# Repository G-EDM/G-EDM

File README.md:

</br>
</br>
</br>

```diff
 ______     _______ ______  _______
|  ____ ___ |______ |     \ |  |  |
|_____|     |______ |_____/ |  |  |      

Overview / Gateway
```                                                               

</br>
</br>

</br>
</br>

# About the project

G-EDM provides Hard- and Software solution for DIY sinker and wire EDM machining targeting the hobby market while trying to keep the project affordable and low budget compatible. While this is one of the main goals there are no compromises made in regards of precision and machine rigidity.

The project evolved over time and so did the mechanical design, the electronics and the firmware.

This repo acts as a gateway to all the other repos and is a way to start the journey into the world of DIY electrical discharge machining.

There are currently two different core version of the electronics and firmware in circulation. The EVOII/III are the initial releases. The new Gapstorm components are the current and upcoming versions. 

Since the sensing circuitry has slightly changed the Gapstorm firmware is not compatible with the EVO pulseboard.

It is possible to upgrade the EVOII and III Pulseboard to match the Gapstorms. A tutorial on how to do that will follow soon. After that upgrade those baords can be used with the new firmware.

</br></br>

# Mechanics

The repo for the new gapstorm router is available here:

[Gapstorm router](https://github.com/G-EDM/gedm-gapstorm/tree/main)

</br></br>

# Electronics

The BOM for the control unit is included on this repo:

[BOM for the control unit](./control-unit-BOM.md)

Files for the PCBs are available on PCBway. To build the electronics it requires two custom PCBs. The switching PCB and the Controlboard aka Motionboard. 

The current PCBs are the Gapstorm Pro Pulseboard and the EVOIII Motionboard.

[Gapstorm Pro Pulseboard on PCBway](https://www.pcbway.com/project/shareproject/G_EDM_Gapstorm_Pro_Pulseboard_a0db8e30.html)

[EVOIII Motionboard on PCBway](https://www.pcbway.com/project/shareproject/W532897ASC41_motionboard_evoIII_rev3_bb113e0f.html)

</br>
All files for the Gapstorm Pro Board are available here:

[Gapstorm Pro Kicad files, Gerbers etc.](https://github.com/G-EDM/Gapstorm-Pro)

</br>
Tip: The Motionboard should be mounted outside of the control box that includes the Pulseboard. One way is shown on the image below using the 3D printed EVOIII Panel.
</br></br>

More images are available here:

[Gapstorm Image gallery](https://gedm.org/photos/1/album/a655d21b876f5ba21783beb6c846ac8f)

</br></br>

# 3D printed control panel

Designed to fit a 2.8" display (see the BOM)

[EVOIII Control panel](https://github.com/G-EDM/G-EDM-EVOIII-Controlpanel)

</br></br>

# Firmware

The Repo for the Gapstorm firmware:

[Gapstorm G-RBL](https://github.com/G-EDM/G-RBLv3)

The Repo for the EVOII and EVOIII Pulseboard firmware (deprecated and not compatible with the gapstorm Pulseboard)

[EVOII/III G-RBL](https://github.com/G-EDM/G-RBL-experimental)

</br></br>

# Spool holder for P5 spools

[P5 Spool holder](https://github.com/G-EDM/spool-controller)

</br></br>

# Wiki

There is no real wiki but I posted some of the most important things on the homepage that will act like some kind of a wiki:

[G-EDM FAQ and Wiki](https://gedm.org/user/1)

</br></br>

# Contact

gedm-support@proton.me

[Join the project on Discord](https://discord.gg/vWSmpkzVrj)

[G-EDM Website](https://gedm.org)

</br>
</br>

# Donations

Bitcoin: bc1qkz8vwrd3pupewdtyg09qj9nv249vlgdy4ffhyv

Paypal: https://www.paypal.com/donate/?hosted_button_id=QP5LHGRUCXXBL

</br>   
</br>

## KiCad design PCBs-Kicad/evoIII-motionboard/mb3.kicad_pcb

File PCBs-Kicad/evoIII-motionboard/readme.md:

# G-EDM EVOIII Motionboard
</br>
</br>
The new EVOIII motionboard passed all tests but was not yet used in any real cutting operation! Use on your own risk and compare the placement
of the components against the schematics. I made the BOM and centroid files very quick and so far the board was not ordered assembled using those files!
</br>
</br>

</br>
</br>
This board comes with a more thoughtful placement of all the breakouts and terminals.

# Changes compared to the EVOII
</br>

    - DIP switches to set the microsteps
    - single JST terminal to connect the motionboard with the pulseboard
    - 200 Ohm current limiting resistors on the feedback pins
    - additional SD card SPI breakout to switch from display SD reader to micro SD reader board (both ways work but only one option at a time)
    - better layout
</br>
</br>
The EVOII is still compatible with everything and not deprecated. EVOII and EVOIII boards can be used.
</br>
</br>
On the circuit itself not much changed except that this board provides a little pin socket to use a micro SD adapter card instead of the display integrated SD reader. Using the displays SD reader still works too.
</br>
</br>
The common micro SD reader boards are build for 5v environments and it needs a little knowledge to get them working with the ESP32s 3.3v levels. I removed the voltage regulator and bridged two pads:
</br>
</br>
https://hackaday.io/project/190371-g-edm/log/240049-testing-the-evoiii-motionboard
</br>
</br>
This way the wires for the display can be longer without risking data loss on the SD channel. But this feature is for testing only and not needed.

How to select the correct Motionboard?

It is a design choice. Go for the one that fits best. The EVOII and EVOIII board provide the same features (except for the new SD card option) and it is more about the terminal and JST connector positions then anything else. The EVOIII board is a little larger.

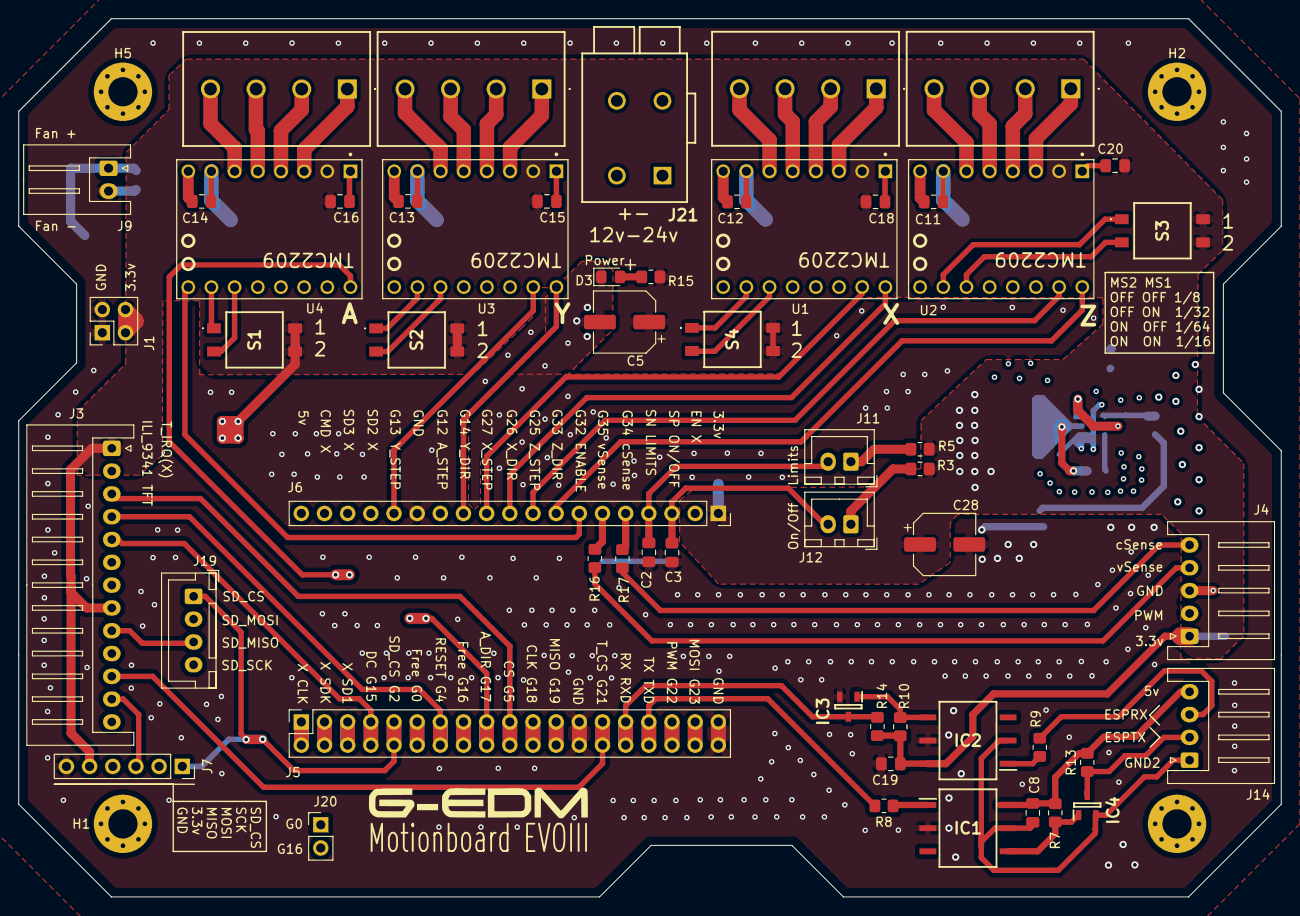
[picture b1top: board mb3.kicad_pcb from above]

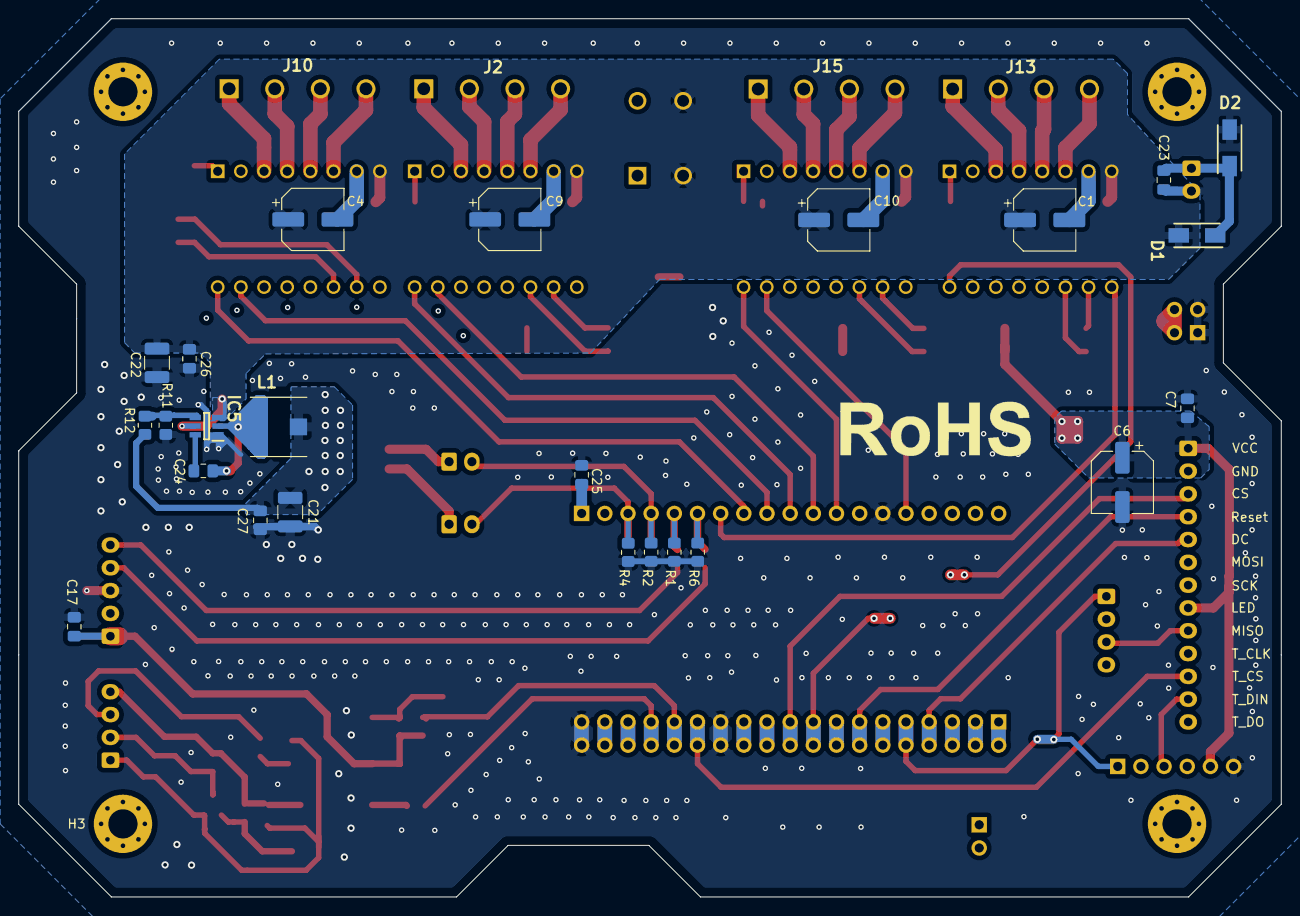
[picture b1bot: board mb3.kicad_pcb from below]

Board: 4 copper layers, 138.4 x 96.3 mm, 83 parts (24 on the bottom side), 73 nets.

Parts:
C1, C4, C9, C10: EEE-HA1V101XP; CP_Elec_6.3x7.7
C2, C3, C7, C8, C11, C12, C13, C14, C15, C16, C17, C18, C19, C20, C23, C24, C25, C26, C27: 08055C104K4T2A; C_0805_2012Metric_Pad1.18x1.45mm_HandSolder
C5, C6, C28: EEE-HA1C221XP; CP_Elec_6.3x7.7
C21: 22uf-16v-X7R (GRM32ER71C226KEA8K); C_1210_3225Metric_Pad1.33x2.70mm_HandSolder
C22: GRM32ER71H475KA88L; C_1210_3225Metric_Pad1.33x2.70mm_HandSolder
D1, D2: RB168L-60TFTE25; DIOM5026X220N
D3: 597-3305-607F; LED_0805_2012Metric_Pad1.15x1.40mm_HandSolder
H1, H2, H3, H5: MountingHole_Pad; MountingHole_3.2mm_M3_Pad_Via
IC1, IC2: H11L1SR2M; SOT254P916X480-6N
IC3, IC4: MMBT3904; SOT95P240X110-3N
IC5: LMR51420XFDDCR; SOT95P280X110-6N
J1: Conn_02x02_Odd_Even; PinHeader_2x02_P2.54mm_Vertical
J2, J10, J13, J15: 796689-4; 7966894
J3: B13B-XH-A(LF)(SN; JST_XH_S13B-XH-A_1x13_P2.50mm_Horizontal
J4: Conn_01x05_Socket; JST_XH_S5B-XH-A_1x05_P2.50mm_Horizontal
J5: PM254-2-19-Z-8.5; PinSocket_2x19_P2.54mm_Vertical
J6: PM254-1-19-Z-8.5; PinSocket_1x19_P2.54mm_Vertical
J7: Conn_01x06_Socket; PinSocket_1x06_P2.54mm_Vertical
J9: B2B-XH-A(LF)(SN); JST_XH_S2B-XH-A_1x02_P2.50mm_Horizontal
J11, J12: B2B-XH-A(LF)(SN); JST_XH_B2B-XH-A_1x02_P2.50mm_Vertical
J14: B4B-XH-A(LF)(SN); JST_XH_S4B-XH-A_1x04_P2.50mm_Horizontal
J19: B4B-XH-A(LF)(SN); JST_XH_B4B-XH-A_1x04_P2.50mm_Vertical
J20: DNP; PinHeader_1x02_P2.54mm_Vertical
J21: 2604-1102; 26041102
L1: 7447786008; WE-PD_6033_6050_PLASTIC_BASE54
R1, R2, R4, R6, R12, R16, R17: 560112120013; R_0805_2012Metric_Pad1.20x1.40mm_HandSolder
R3, R5: ERJ-T06J102V; R_0805_2012Metric_Pad1.20x1.40mm_HandSolder
R7, R10, R14: RCC0805470RFKEA; R_0805_2012Metric_Pad1.20x1.40mm_HandSolder
R8, R13: RCC0805330RFKEA; R_0805_2012Metric_Pad1.20x1.40mm_HandSolder
R9: MR08X4990FTL; R_0805_2012Metric_Pad1.20x1.40mm_HandSolder
R11: 560112120026; R_0805_2012Metric_Pad1.20x1.40mm_HandSolder
R15: ERJ-T06J221V; R_0805_2012Metric_Pad1.20x1.40mm_HandSolder
S1, S2, S3, S4: 2454985-2; 24549852
U1, U2, U3, U4: TMC2209; MODULE_TMC2209_SILENTSTEPSTICK

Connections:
3.3v+: C5.1, C6.1, C7.1, C15.1, C16.1, C17.1, C18.1, C19.2, C20.1, C21.2, C25.1, C27.2, C28.1, IC2.6 (VCC), J1.3, J1.4, J3.1, J3.8, J4.1, J6.1, J7.5, L1.2, R3.2, R5.2, R10.1, R12.1, R14.2, R15.1, S1.B1 (3), S1.B2 (4), S2.B1 (3), S2.B2 (4), S3.B1 (3), S3.B2 (4), S4.B1 (3), S4.B2 (4), U1.2 (VIO), U2.2 (VIO), U3.2 (VIO), U4.2 (VIO)
12v+: C1.1, C4.1, C9.1, C10.1, C11.1, C12.1, C13.1, C14.1, C22.2, C26.2, D1.2 (A), IC5.3 (VIN), IC5.5 (EN), J21.3 (2.1), J21.4 (2.2), U1.8 (VM), U2.8 (VM), U3.8 (VM), U4.8 (VM)
CLK: J3.7, J3.10, J5.21, J5.22, J7.2, J19.4
CS: J3.3, J5.19, J5.20
DC: J3.5, J5.7, J5.8
DPMRXB: IC4.3 (COLLECTOR), J14.2, R13.1
DPMTXB: J14.3, R9.1
GND: C1.2, C2.2, C3.2, C4.2, C5.2, C6.2, C7.2, C9.2, C10.2, C11.2, C12.2, C13.2, C14.2, C15.2, C16.2, C17.2, C18.2, C19.1, C20.2, C21.1, C22.1, C23.2, C25.2, C26.1, C27.1, C28.2, D2.2 (A), D3.1 (K), IC1.2 (CATHODE), IC2.5 (GND), IC3.2 (EMITTER), IC5.1 (GND), J1.1, J1.2, J3.2, J4.3, J5.25, J5.26, J5.37, J5.38, J6.14, J7.6, J9.2, J21.1 (1.1), J21.2 (1.2), R1.2, R2.2, R4.2, R6.2, R11.2, U1.1 (GND), U1.7 (GND), U2.1 (GND), U2.7 (GND), U3.1 (GND), U3.7 (GND), U4.1 (GND), U4.7 (GND)
GND5v: C8.1, IC1.5 (GND), IC2.2 (CATHODE), IC4.2 (EMITTER), J14.1
GPIO16: J5.15, J5.16, J20.2
Limit39: C2.1, J6.4, J11.2, R2.1
MOSI: J3.6, J3.12, J5.35, J5.36, J7.3, J19.2
Miso: J3.9, J3.13, J5.23, J5.24, J7.4, J19.3
unnamed: C23.1, D1.1 (K), D2.1 (K), J9.1
unnamed: D3.2 (A), R15.2
unnamed: IC1.1 (ANODE), R8.2
unnamed: IC1.4 (VO), IC4.1 (BASE), R7.2
unnamed: IC2.1 (ANODE), R9.2
unnamed: IC2.4 (VO), IC3.1 (BASE), R10.2
unnamed: C24.1, IC5.6 (CB)
unnamed: IC5.4 (FB), R11.1, R12.2
unnamed: C24.2, IC5.2 (SW), L1.1
unnamed: J4.4, R16.1
unnamed: J4.5, R17.1
unnamed: J5.1, J5.2
unnamed: J5.3, J5.4
unnamed: J5.5, J5.6
unnamed: J11.1, R5.1
unnamed: J12.1, R3.1
unnamed: J2.2, U1.4 (M1A)
unnamed: J2.1, U1.3 (M1B)
unnamed: J2.3, U1.5 (M2A)
unnamed: J2.4, U1.6 (M2B)
unnamed: J10.2, U2.4 (M1A)
unnamed: J10.1, U2.3 (M1B)
unnamed: J10.3, U2.5 (M2A)
unnamed: J10.4, U2.6 (M2B)
unnamed: J15.2, U3.4 (M1A)
unnamed: J15.1, U3.3 (M1B)
unnamed: J15.3, U3.5 (M2A)
unnamed: J15.4, U3.6 (M2B)
unnamed: J13.2, U4.4 (M1A)
unnamed: J13.1, U4.3 (M1B)
unnamed: J13.3, U4.5 (M2A)
unnamed: J13.4, U4.6 (M2B)
PWM: J4.2, J5.33, J5.34
RX(IO3): IC3.3 (COLLECTOR), J5.29, J5.30, R14.1
SD_CS: J5.9, J5.10, J7.1, J19.1
Start36: C3.1, J6.3, J12.2, R4.1
TX(IO1): J5.31, J5.32, R8.1
T_CS: J3.11, J5.27, J5.28
VCCB: C8.2, IC1.6 (VCC), J14.4, R7.1, R13.2
adir17: J5.17, J5.18, U4.9 (DIR)
ams1: S1.A1 (1), U4.15 (MS1)
ams2: S1.A2 (2), U4.14 (MS2)
astep12: J6.13, U4.10 (STEP)
enable-all: J6.7, U1.16 (~EN), U2.16 (~EN), U3.16 (~EN), U4.16 (~EN)
gpio0: J5.11, J5.12, J20.1
input35: J6.6, R6.1, R16.2
reset: J3.4, J5.13, J5.14
vSense34: J6.5, R1.1, R17.2
xdir: J6.10, U1.9 (DIR)
xms1: S4.A1 (1), U1.15 (MS1)
xms2: S4.A2 (2), U1.14 (MS2)
xstep: J6.11, U1.10 (STEP)
ydir: J6.12, U3.9 (DIR)
yms1: S2.A1 (1), U3.15 (MS1)
yms2: S2.A2 (2), U3.14 (MS2)
ystep: J6.15, U3.10 (STEP)
zdir: J6.8, U2.9 (DIR)
zms1: S3.A1 (1), U2.15 (MS1)
zms2: S3.A2 (2), U2.14 (MS2)
zstep: J6.9, U2.10 (STEP)

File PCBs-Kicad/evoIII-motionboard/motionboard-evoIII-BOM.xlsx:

|  |  | xxxx xxxx xxxxx xxPCS BOM (Sample Bill of Materials)
Item # | *Designator | *Qty | Manufacturer | *Mfg Part # | Description / Value | *Package/Footprint | Type | Your Instructions / Notes | PCBWay Update
1 | C3,C19,C18,C15,C2,C13,C12,C14,C16,C11,C20,C8,C27,C25,C26,C17,C23,C7,C24 | 19 |  | 08055C104K4T2A | 0.1uf-50v-x7r 08055C104K4T2A | C_0805_2012Metric_Pad1.18x1.45mm_HandSolder
2 | C22 | 1 |  | GRM32ER71H475KA88L | 4.7uf-50v-X7R GRM32ER71H475KA88L | C_1210_3225Metric_Pad1.33x2.70mm_HandSolder
3 | C21 | 1 |  | GRM32ER71C226KEA8K | 22uf-16v-X7R GRM32ER71C226KEA8K | C_1210_3225Metric_Pad1.33x2.70mm_HandSolder
4 | C1,C4,C9,C10 | 4 |  | EEE-HA1V101XP | 100uf35v-6.3x7.7mm EEE-HA1V101XP | CP_Elec_6.3x7.7
5 | C5,C28,C6 | 3 |  | EEE-HA1C221XP | 220uf16v-6.3x7.7mm EEE-HA1C221XP | CP_Elec_6.3x7.7
6 | R8,R13 | 2 |  | RCC0805330RFKEA | 330 Ohm 1% RCC0805330RFKEA | R_0805_2012Metric_Pad1.20x1.40mm_HandSolder
7 | R7,R10,R14 | 3 |  | RCC0805470RFKEA | 470 Ohm 1% RCC0805470RFKEA | R_0805_2012Metric_Pad1.20x1.40mm_HandSolder
8 | R12,R4,R6,R1,R2 | 5 |  | 560112120013 | 100 kOhm 1% WRIS-RSKS 560112120013 | R_0805_2012Metric_Pad1.20x1.40mm_HandSolder
9 | R17,R16 | 2 |  | 560112120015 | 200 Ohm 1% WRIS-RSKS 560112120015 | R_0805_2012Metric_Pad1.20x1.40mm_HandSolder
10 | R9 | 1 |  | MR08X4990FTL | 499 Ohm 1% MR08X4990FTL | R_0805_2012Metric_Pad1.20x1.40mm_HandSolder
11 | R3,R5 | 2 |  | ERJ-T06J102V | 1kOhm 5% ERJ-T06J102V | R_0805_2012Metric_Pad1.20x1.40mm_HandSolder
12 | R11 | 1 |  | 560112120026 | 22.1k 1% W眉rth WRIS-RSKS 560112120026 | R_0805_2012Metric_Pad1.20x1.40mm_HandSolder
13 | R15 | 1 |  | ERJ-T06J221V | 220 Ohm 5% ERJ-T06J221V | R_0805_2012Metric_Pad1.20x1.40mm_HandSolder
14 | U4 Socket,U1 Socket,U3 Socket,U2 Socket | 8 |  | BKL 10122206 | 2604 | PinSocket_1x08_P2.54mm_Vertical
15 | U4,U1,U3,U2 | 0 |  |  | TMC2209 | MODULE_TMC2209_SILENTSTEPSTICK |  |  | DNP
16 | J21 | 1 |  | WAGO 2604-1102 | WAGO 2604-1102 | 26041102
17 | J19 | 1 |  | B4B-XH-A(LF)(SN) | JST XHP-4 | JST_XH_B4B-XH-A_1x02_P2.50mm_Vertical
18 | J12,J11 | 2 |  | B2B-XH-A(LF)(SN) | JST XHP-2 | JST_XH_B2B-XH-A_1x02_P2.50mm_Vertical
19 | J14 | 1 |  | S4B-XH-A(LF)(SN) | JST XHP-4 | JST_XH_S4B-XH-A_1x04_P2.50mm_Horizontal
20 | J4 | 1 |  | S5B-XH-A(LF)(SN) | JST XHP-5 | JST_XH_S5B-XH-A_1x05_P2.50mm_Horizontal
21 | J3 | 1 |  | S13B-XH-A(LF)(SN) | JST XHP-13 | JST_XH_S13B-XH-A_1x05_P2.50mm_Horizontal
22 | J9 | 1 |  | S2B-XH-A(LF)(SN) | JST XHP-2 | JST_XH_S2B-XH-A_1x02_P2.50mm_Horizontal
23 | J7 | 1 |  | BL 1X06G8 2,54 | 2,54mm pin socket 1x06 | PinSocket_1x06_P2.54mm_Vertical
24 | J1 | 1 |  | 10-97-7046 | 2,54mm pin header 2x02 | PinHeader_2x02_P2.54mm_Vertical
25 | J20 | 0 |  |  | Not used | PinHeader_1x02_P2.54mm_Vertical |  |  | DNP
26 | J15,J13,J2,J10 | 4 |  | TE Connectivity 796689-4 | 35掳 4-pole screw terminal ( TE Connectivity 796689-4 ) | TerminalBlock_Phoenix_MKDS-1,5-4_1x04_P5.00mm_Horizontal
27 | J6 | 1 |  | BL 1X20G8 2,54 | 2,54mm pin socket 1x19 (1x20 cutted) BL 1X20G8 2,54 | PinSocket_1x19_P2.54mm_Vertical
28 | J5 | 1 |  | BKL 10120963 | 2,54mm pin socket 2x19 (2x20 cutted) BKL 10120963 | PinSocket_2x19_P2.54mm_Vertical
29 | S2,S4,S3,S1 | 4 |  | TE Connectivity 2454985-2 | SMD Dip switch 2 pos, gull wing | DIP-2
30 | D3 | 1 |  | 597-3305-607F | 597-3305-607F | LED_0805_2012Metric_Pad1.15x1.40mm_HandSolder
31 | D1,D2 | 2 |  | RB168L-60TFTE25 | Schottky Diodes & Rectifiers DO214 60V 1A AUTO SCHOTTKY | DO-214AC-2
32 | L1 | 1 |  | 7447786008 | SMD WE-PD 8.2uH 2.3A | WE-PD_6033_6050_PLASTIC_BASE54
33 | IC5 | 1 |  | LMR51420XFDDCR | SIMPLE SWITCHER power converter LMR51420XFDDCR | SOT95P280X110-6N
34 | IC3,IC4 | 2 |  | MMBT3904 | NPN transistor MMBT3904 | SOT95P240X110-3N
35 | IC1,IC2 | 2 |  | H11L1SR2M | H11L1SR2M | SOT254P916X480-6N
 | / | 1 |  |  |  | AZ delivery 38Pin ESP32 NodeMCU WLAN Development Dev Kit C WiFi Bluetooth Board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 |  | https://www.ebay.de/itm/144215008485 | DNP
 | / | 1 |  |  |  | Silentstepstick TMC2209 |  |  | DNP
Need a quick and accurante quote? Need an efficient production? Please read SMT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
Click for Instructions on How to Create a BOM

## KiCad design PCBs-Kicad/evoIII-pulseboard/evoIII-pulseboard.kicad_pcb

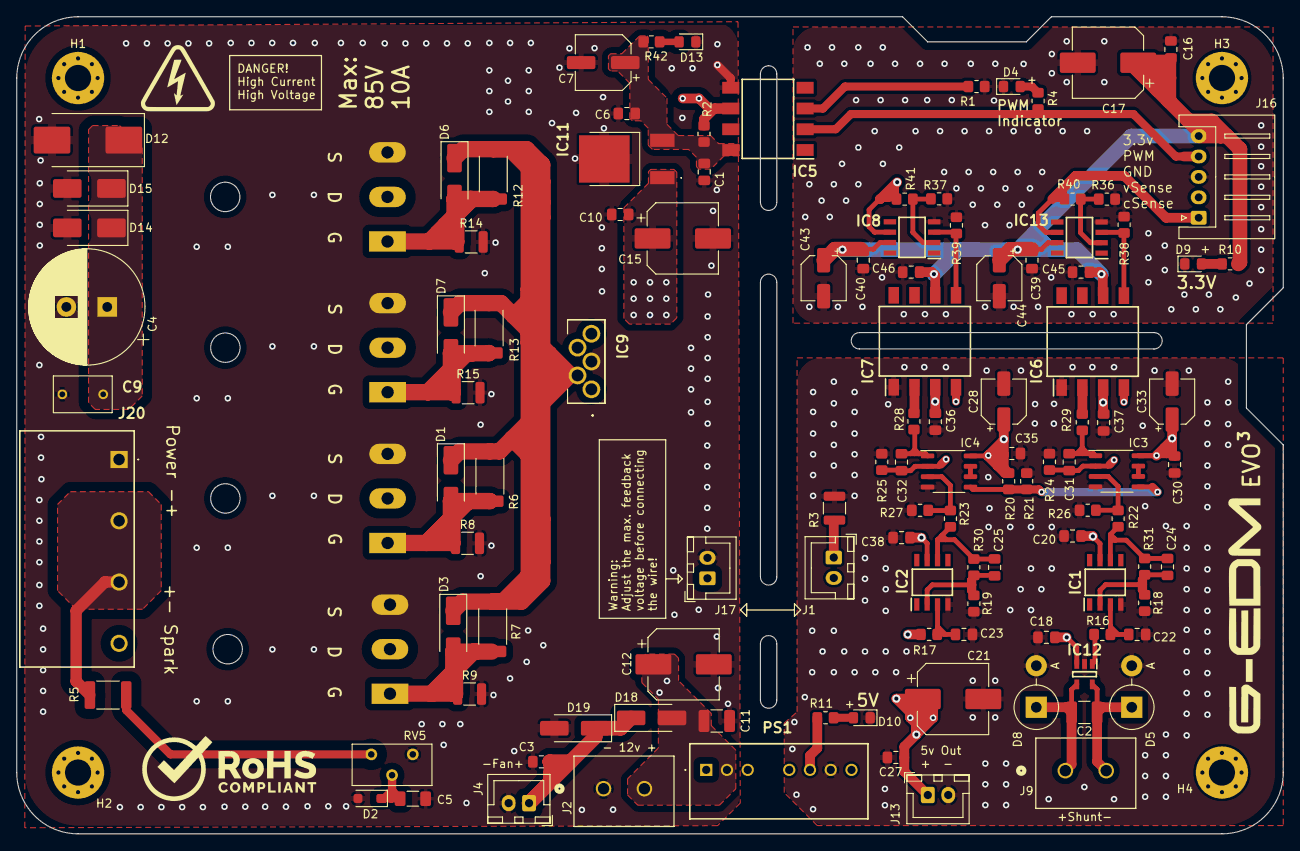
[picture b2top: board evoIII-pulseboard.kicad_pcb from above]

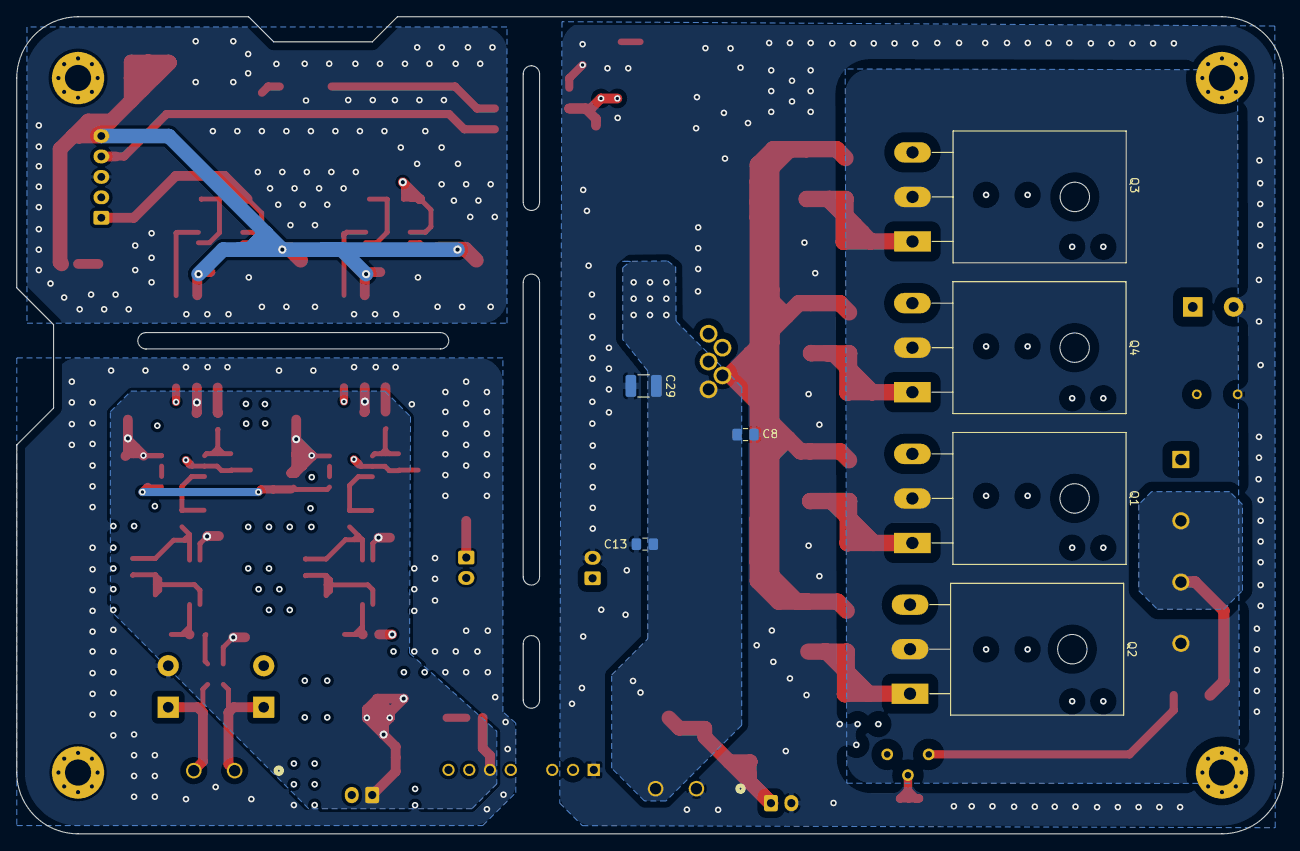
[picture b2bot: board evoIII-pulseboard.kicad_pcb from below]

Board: 4 copper layers, 155.0 x 100.0 mm, 124 parts (7 on the bottom side), 52 nets.

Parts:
C1, C3, C6, C8, C10, C13, C16, C18, C20, C27, C30, C35, C36, C37, C38, C39, C40, C45, C46: 08055C104K4T2A; C_0805_2012Metric_Pad1.18x1.45mm_HandSolder
C2: 12107A101JAT2A; C_1210_3225Metric_Pad1.33x2.70mm_HandSolder
C4: DNP; CP_Radial_D14.0mm_P5.00mm
C5: DNP; C_1206_3216Metric_Pad1.33x1.80mm_HandSolder
C7: EEE-HAC221XAP; CP_Elec_6.3x7.7
C9: FKP2F004701D00JSSD; FKP2G011001D00KI00
C11, C29: GRM32RR71H105KA01K; C_1210_3225Metric_Pad1.33x2.70mm_HandSolder
C12, C15, C17, C21: EEE-HAV221UAP; CP_Elec_8x10.5
C22, C23, C31, C32: C0805C101J5RACTU; C_0805_2012Metric_Pad1.18x1.45mm_HandSolder
C24, C25: DNP; C_0805_2012Metric_Pad1.18x1.45mm_HandSolder
C28, C33, C43, C44: AVS476M16C12T-F; CP_Elec_5x5.4
D1, D3, D6, D7, D18, D19: B360A-E3/61T; D_SMA_Handsoldering
D2: DNP; D_SOD-123F
D4: APT2012LVBC/D; LED_0805_2012Metric_Pad1.15x1.40mm_HandSolder
D5, D8: 1N5378B; D_DO-201_P5.08mm_Vertical_AnodeUp
D9, D10, D13: SM0805UGC; LED_0805_2012Metric_Pad1.15x1.40mm_HandSolder
D12: MB520_R1_00001; D_SMC_Handsoldering
D14, D15: SMBJ5378B-TP; D_SMB_Handsoldering
H1, H2, H4: MountingHole; MountingHole_3.2mm_M3_Pad_Via
H3: MountingHole_Pad; MountingHole_3.2mm_M3_Pad_Via
IC1, IC2, IC8, IC13: OPA350UA; SOIC127P600X175-8N
IC3, IC4: LM358F-GE2; SOP-8_3.9x4.9mm_P1.27mm
IC5: 6N137S; SOP254P1016X460-8N
IC6, IC7: HCNR201-500E; SOP254P1230X400-8N
IC9: IXDI609CI
IC11: MC7805CDTRKG; MJD1221G
IC12: INA293B3; SOT95P280X145-5N
J1, J13, J17: B2B-XH-A(LF)(SN); JST_XH_B2B-XH-A_1x02_P2.50mm_Vertical
J2: 1776138-2 and 796641-2; CONN2_796643-2_TEC
J4: S2B-XH-A(LF)(SN); JST_XH_B2B-XH-A_1x02_P2.50mm_Vertical
J9: 1776138-2, 796641-2; CONN2_796643-2_TEC
J16: S5B-XH-A(LF)(SN); JST_XH_S5B-XH-A_1x05_P2.50mm_Horizontal
J20: 8000078309, 8000078355; 8000078309
PS1: RS3K-2405SZ/H3; RS3K2405SZH3
Q1, Q2, Q3, Q4: IRFP260NPBF; TO-247-3_Horizontal_TabUp
R1, R28, R29: 560112120015; R_0805_2012Metric_Pad1.20x1.40mm_HandSolder
R2, R20, R21, R22, R23: 560112120004; R_0805_2012Metric_Pad1.20x1.40mm_HandSolder
R3: CRCW12101K00JNEAIF; R_1210_3225Metric
R4, R10: ERJ-T06J221V; R_0805_2012Metric_Pad1.20x1.40mm_HandSolder
R5: ERJ-U12F1001U; R_1812_4532Metric_Pad1.30x3.40mm_HandSolder
R6, R7, R12, R13: RC2512JK-7W4R7L; R_2512_6332Metric_Pad1.40x3.35mm_HandSolder
R8, R9, R14, R15: RK73B2ETTD104J; R_1210_3225Metric
R11, R42: RK73B2ATTD561J; R_0805_2012Metric_Pad1.20x1.40mm_HandSolder
R16, R17, R18, R19: RCC08051K00FKEA; R_0805_2012Metric_Pad1.20x1.40mm_HandSolder
R24, R25, R38, R39: 560112120013; R_0805_2012Metric_Pad1.20x1.40mm_HandSolder
R26, R27: RCC08054K70FKEA; R_0805_2012Metric_Pad1.20x1.40mm_HandSolder
R30, R31: RCC08050000Z0EA; R_0805_2012Metric_Pad1.20x1.40mm_HandSolder
R36, R37, R40, R41: RK73H2ARTTD2002F; R_0805_2012Metric_Pad1.20x1.40mm_HandSolder
RV5: 3296Y-1-103LF; Potentiometer_Bourns_3296Y_Vertical

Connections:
2.5V: IC3.5 (2IN+), IC4.5 (2IN+), R20.2, R21.1
5v: C1.1, C6.1, C7.1, IC5.8 (VCC), IC11.3 (OUTPUT), R2.1, R42.2
5v-optoout: IC5.6 (VO), IC9.4 (IN), R2.2
12vpower: C8.1, C10.1, C11.1, C12.1, C13.1, C15.1, C29.1, D18.2 (A), IC9.1 (VCC), IC11.1 (INPUT), J2.2, PS1.2 (+VIN)
+48V: C4.1, C9.2, D12.1 (K), D14.1 (K), D15.1 (K), J20.2, J20.3, R5.1
ESP3.3v: C16.1, C17.1, C39.1, C40.1, C43.1, C44.1, C45.1, C46.1, IC6.6 (PD2_CATHODE), IC7.6 (PD2_CATHODE), IC8.7 (V+), IC13.7 (V+), J16.5, R10.2
GND1: C16.2, C17.2, C39.2, C40.2, C43.2, C44.2, C45.2, C46.2, D4.1 (K), D9.1 (K), IC8.4 (V-), IC13.4 (V-), J16.3, R1.2, R36.1, R37.1, R38.1, R39.1
GND2: C1.2, C3.1, C4.2, C5.2, C6.2, C7.2, C8.2, C9.1, C10.2, C11.2, C12.2, C13.2, C15.2, C29.2, D2.2 (A), D12.2 (A), D13.1 (K), D14.2 (A), D15.2 (A), D19.2 (A), IC5.5 (GND), IC9.3 (GND), IC11.2 (GROUND), J2.1, J4.2, J17.2, J20.1, PS1.1 (-VIN), Q1.3 (S), Q2.3 (S), Q3.3 (S), Q4.3 (S), R8.2, R9.2, R14.2, R15.2, RV5.1
GND3: C18.1, C20.2, C21.2, C22.2, C23.2, C27.2, C28.2, C30.2, C33.2, C35.1, C36.1, C37.1, C38.1, D5.2 (A), D8.2 (A), D10.1 (K), IC1.4 (V-), IC2.4 (V-), IC3.4 (GND), IC4.4 (GND), IC6.1 (LED_CATHODE), IC7.1 (LED_CATHODE), IC12.2 (GND), J13.2, PS1.7 (-VOUT), R3.1, R18.2, R19.2, R21.2, R24.1, R25.1, R26.2, R27.2
Gatedriverout: D1.1 (K), D3.1 (K), D6.1 (K), D7.1 (K), IC9.2 (~OUT), R6.2, R7.2, R12.2, R13.2
ISO+5v: C18.2, C20.1, C21.1, C27.1, C28.1, C30.1, C33.1, C35.2, C36.2, C37.2, C38.2, IC1.7 (V+), IC2.7 (V+), IC3.8 (VCC), IC4.8 (VCC), IC6.3 (PD1_CATHODE), IC7.3 (PD1_CATHODE), IC12.3 (VS), J13.1, PS1.6 (+VOUT), R11.2, R20.1
Isolated-csense-out: IC13.6 (OUTPUT), J16.1, R40.2
Isolated-vsense-out: IC8.6 (OUTPUT), J16.2, R41.2
unnamed: D1.2 (A), Q1.1 (G), R6.1, R8.1
unnamed: C5.1, D2.1 (K), J17.1, RV5.2
unnamed: D3.2 (A), Q2.1 (G), R7.1, R9.1
unnamed: D4.2 (A), R4.1
unnamed: C2.1, D5.1 (K), IC12.5 (IN-), J9.2
unnamed: D6.2 (A), Q3.1 (G), R12.1, R14.1
unnamed: D7.2 (A), Q4.1 (G), R13.1, R15.1
unnamed: C2.2, D8.1 (K), IC12.4 (IN+), J9.1
unnamed: D9.2 (A), R10.1
unnamed: D10.2 (A), R11.1
unnamed: D13.2 (A), R42.1
unnamed: C3.2, D18.1 (K), D19.1 (K), J4.1
unnamed: C22.1, IC1.3 (+IN), R16.2
unnamed: C24.2, IC1.2 (-IN), R18.1, R31.2
unnamed: C24.1, IC1.6 (OUTPUT), R22.2, R31.1
unnamed: C23.1, IC2.3 (+IN), R17.2
unnamed: C25.2, IC2.2 (-IN), R19.1, R30.2
unnamed: C25.1, IC2.6 (OUTPUT), R23.2, R30.1
unnamed: IC3.3 (1IN+), R22.1, R26.1
unnamed: C31.1, IC3.2 (1IN-), IC6.4 (PD1_ANODE), R24.2
unnamed: C31.2, IC3.1 (1OUT), R29.2
unnamed: IC3.6 (2IN-), IC3.7 (2OUT)
unnamed: IC4.3 (1IN+), R23.1, R27.1
unnamed: C32.1, IC4.2 (1IN-), IC7.4 (PD1_ANODE), R25.2
unnamed: C32.2, IC4.1 (1OUT), R28.2
unnamed: IC4.6 (2IN-), IC4.7 (2OUT)
unnamed: IC5.3 (CATHODE), R1.1
unnamed: IC6.2 (LED_ANODE), R29.1
unnamed: IC7.2 (LED_ANODE), R28.1
unnamed: IC7.5 (PD2_ANODE), IC8.3 (+IN), R39.2
unnamed: IC8.2 (-IN), R37.2, R41.1
unnamed: IC12.1 (OUT), R16.1
unnamed: IC6.5 (PD2_ANODE), IC13.3 (+IN), R38.2
unnamed: IC13.2 (-IN), R36.2, R40.1
unnamed: J1.1, R3.2
unnamed: J1.2, R17.1
unnamed: R5.2, RV5.3
pwm-in: IC5.2 (ANODE), J16.4, R4.2
spark-minus-to-drain: J20.4, Q1.2 (D), Q2.2 (D), Q3.2 (D), Q4.2 (D)

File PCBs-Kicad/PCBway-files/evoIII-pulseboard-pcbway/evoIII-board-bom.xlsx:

|  |  | G-EDM EVOII Sensorboard – BOM
Item # | *Designator | *Qty | Manufacturer | *Mfg Part # | Description / Value | *Package/Footprint | Type | Comments
16 | C31,C32,C23,C22 | 4 | KEMET | C0805C101J5RACTU | Multilayer Ceramic Capacitors MLCC - SMD/SMT 50V 100pF X7R 0805 5% | C_0805_2012Metric_Pad1.18x1.45mm_HandSolder | SMD
2 | C1,C3,C6,C8,C10,C13,C16,C18,C20,C27,C30,C35,C36,C37,C38,C39,C40,C45,C46 | 19 | KYOCERA AVX | 08055C104K4T2A | Multilayer Ceramic Capacitors MLCC - SMD/SMT 50V 0.1uF X7R | C_0805_2012Metric_Pad1.18x1.45mm_HandSolder | SMD
36 | C25,C24 | 0 |  | DNP | DNP | C_0805_2012Metric_Pad1.18x1.45mm_HandSolder | SMD | DNP
39 | C11,C29 | 2 | Murata Electronics | GRM32RR71H105KA01K | Multilayer Ceramic Capacitors MLCC - SMD/SMT 1 uF 50 VDC 10% 1210 X7R | C_1210_3225Metric_Pad1.33x2.70mm_HandSolder | THT
15 | C2 | 1 | KYOCERA AVX | 12107A101JAT2A | Multilayer Ceramic Capacitors MLCC – SMD/SMT 500V 100pF | C_1210_3225Metric_Pad1.33x2.70mm_HandSolder | SMD
4 | C28,C33,C44,C43 | 4 | Panasonic | EEEHA1C470WR | Aluminium Electrolytic Capacitors - SMD 16V 47uF | CP_Elec_5x5.4 | SMD
5 | C12,C15,C17,C21 | 4 | Panasonic | EEE-HAV221UAP | Aluminium Electrolytic Capacitors - SMD 220UF 35V | CP_Elec_8x10.5 | SMD
43 | C7 | 1 | Panasonic | EEE-HAC221XAP | Aluminium Electrolytic Capacitors - SMD 220UF 16V HA SMD | CP_Elec_6.3x7.7 | SMD
35 | R30,R31 | 2 | Vishay / Dale | RCC08050000Z0EA | Thick Film Resistors - SMD Zero ohm Jumper | R_0805_2012Metric_Pad1.20x1.40mm_HandSolder | SMD
9 | R4,R10 | 2 | Panasonic | ERJ-T06J221V | Thick Film Resistors - SMD 0805 220ohms 5% | R_0805_2012Metric_Pad1.20x1.40mm_HandSolder | SMD
20 | R11,R42 | 2 | KOA Speer | RK73B2ATTD561J | Thick Film Resistors - SMD 1/4watts 560ohms 5% | R_0805_2012Metric_Pad1.20x1.40mm_HandSolder | SMD
12 | R8,R9,R14,R15 | 4 | KOA Speer | RK73B2ETTD104J | Thick Film Resistors - SMD 1/2W 100Kohms 5% | R_1210_3225Metric | SMD
1 | R16,R17,R18,R19 | 4 | Vishay / Dale | RCC08051K00FKEA | Thick Film Resistors - SMD 1/4W 1Kohms 1% 100ppm | R_0805_2012Metric_Pad1.20x1.40mm_HandSolder | SMD
32 | R27,R26 | 2 | Vishay / Dale | RCC08054K70FKEA | Thick Film Resistors - SMD 1/4W 4.7Kohms 1% 100ppm | R_0805_2012Metric_Pad1.20x1.40mm_HandSolder | SMD
3 | R40,R41,R36,R37 | 4 | KOA Speer | RK73H2ARTTD2002F | Thick Film Resistors - SMD 1/4W 20K OHM 1% | R_0805_2012Metric_Pad1.20x1.40mm_HandSolder | SMD
19 | R24,R25,R38,R39 | 4 | Würth Elektronik | 560112120013 | Thick Film Resistors - SMD WRIS-RSKS 100 kOhms 1 % 0.25 W 0805 | R_0805_2012Metric_Pad1.20x1.40mm_HandSolder | SMD
23 | R2,R20,R21,R22,R23 | 5 | Würth Elektronik | 560112120004 | Thick Film Resistors - SMD WRIS-RSKS 10 kOhms 1 % 0.25 W 0805 | R_0805_2012Metric_Pad1.20x1.40mm_HandSolder | SMD
28 | R1,R28,R29 | 3 | Würth Elektronik | 560112120015 | Thick Film Resistors - SMD WRIS-RSKS 200 Ohms 1 % 0.25 W 0805 | R_0805_2012Metric_Pad1.20x1.40mm_HandSolder | SMD
34 | R3 | 1 | Vishay / Dale | CRCW12101K00JNEAIF | Thick Film Resistors - SMD 1kOhm 5% | R_1210_3225Metric | SMD
7 | R13,R12,R6,R7 | 4 | YAGEO | RC2512JK-7W4R7L | Thick Film Resistors - SMD 4.7 Ohms 2 W 2512 5% | R_2512_6332Metric_Pad1.40x3.35mm_HandSolder | SMD
13 | R5 | 1 | Panasonic | ERJ-U12F1001U | Thick Film Resistors - SMD 1812 1% 1.0Kohm | R_1812_4532Metric_Pad1.30x3.40mm_HandSolder | SMD
40 | D4 | 1 | Kingbright | APT2012LVBC/D | Standard LEDs - SMD 2.0X1.2MM LOW CRNT | LED_0805_2012Metric_Pad1.15x1.40mm_HandSolder | SMD
29 | D10,D9,D13 | 3 | Bivar | SM0805UGC | Standard LEDs - SMD Ultra Green 525 nm Water Clear, 20mA, 2v | LED_0805_2012Metric_Pad1.15x1.40mm_HandSolder | SMD
44 | D12 | 1 | Panjit | MB520_R1_00001 | Schottky Diodes & Rectifiers 200V,Schottky,SMC,5A | D_SMC_Handsoldering | SMD
31 | D14,D15 | 2 | Micro Commercial Components (MCC) | SMBJ5378B-TP | Zener Diodes 5W ZENERS SMB, 100V | D_SMB_Handsoldering | SMD
38 | D8,D5 | 2 | onsemi | 1N5378B | Zener Diodes 100V 5W | D_DO-201_P5.08mm_Vertical_AnodeUp | THT
25 | D1,D3,D6,D7,D18,D19 | 6 | Vishay General Semiconductor | B360A-E3/61T | Schottky Diodes & Rectifiers 60 Volt 3.0 Amp 50 Amp IFSM | D_SMA_Handsoldering | SMD
26 | IC12 | 1 | Texas Instruments | INA293B3 | Current Sense Amplifiers AEC-Q100, -4-V to 110-V, 1.3-MHz, ultra-precise curren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 | SOT95P280X145-5N | SMD
30 | IC11 | 1 | onsemi | MC7805CDTRKG | Linear Voltage Regulators 5V 1A Positive | MJD1221G | SMD
6 | IC1,IC13,IC2,IC8 | 4 | Texas Instruments | OPA350UA | High Speed Operational Amplifiers Hi-Spd Single-Sply Rail-to-Rail | SOIC127P600X175-8N | SMD
10 | IC5 | 1 | Lite-On | 6N137S | High Speed Optocouplers High Speed 10MBd LogicGate Output | SOP254P1016X460-8N | SMD
11 | IC6,IC7 | 2 | Broadcom / Avago | HCNR201-500E | High Linearity Optocouplers 1 Ch 60mW 25mA | SOP254P1230X400-8N | SMD
17 | IC4,IC3 | 2 | ROHM Semiconductor | LM358F-GE2 | Operational Amplifiers - Op Amps Dual Grnd Sense Op Amp SOP8 | SOP-8_3.9x4.9mm_P1.27mm | SMD
33 | IC9 | 1 | IXYS Integrated Circuits | IXDI609CI | Gate Drivers 9-Ampere Low-Side Ultrafast MOSFET inverting | IXDI609CI | THT
21 | J20 | 1 | Weidmüller | 8000078309 | Pluggable Terminal Blocks PCB plug-in connector (board connection), 7.50 mm, Nu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 | 8000078309 | THT
22 | J20 | 1 | Weidmüller | 8000078355 | Pluggable Terminal Blocks MPS 7S/04 S F2 TN B B
8 | J4 | 1 | JST Commercial | S2B-XH-A(LF)(SN) | JST Automotive Connector | JST_XH_B2B-XH-A_1x02_P2.50mm_Vertical | THT
14 | J13,J17,J1 | 3 | JST Commercial | B2B-XH-A(LF)(SN) | CONN HEADER VERT 2POS 2.5MM | JST_XH_B2B-XH-A_1x02_P2.50mm_Vertical | THT
37 | J16 | 1 | JST Commercial | S5B-XH-A(LF)(SN) | JST Automotive Connector | JST_XH_S5B-XH-A_1x05_P2.50mm_Horizontal | THT
41 | J2,J9 | 2 | TE Connectivity / AMP | 1776138-2 | Pluggable Terminal Blocks 2P TERMI-BLOK HDR HIGH TEMP (board connection) | CONN2_796643-2_TEC | THT
42 | J2,J9 | 2 | TE Connectivity / AMP | 796641-2 | Pluggable Terminal Blocks 2 POS 5.0 MM R/A PLUG TRM BLK | CONN2_796643-2_TEC | THT
27 | C9 | 1 | WIMA | FKP2F004701D00JSSD | Film Capacitors 250V 470pF 5%, 5mm lead spacing | FKP2F004701D00JSSD | THT
24 | C5 | 0 |  | DNP | DNP | C_1206_3216Metric_Pad1.33x1.80mm_HandSolder | SMD | DNP
45 | C4 | 0 |  | DNP | DNP | CP_Radial_D14.0mm_P5.00mm | THT | DNP
46 | D2 | 1 |  | DNP | DNP | D_SOD-123F | SMD | DNP
47 | RV5 | 1 | Bourns | 3296Y-1-103LF | Trimmer Resistors - Through Hole 3/8" 10Kohms Sealed Vertical Adjust | Potentiometer_Bourns_3296Y_Vertical | THT
48 | PS1 | 1 | RECOM Power | RS3K-2405SZ/H3 | Isolated DC/DC Converters - Through Hole 3W 9-36Vin 5Vout 600mA | RS3K2405SZH3 | THT
51 | Q3,Q2,Q4,Q1 | 4 | Infineon Technologies | IRFP260NPBF | MOSFETs MOSFT 200V 49A 40mOhm 156nCAC | TO-247-3_Horizontal_TabUp | THT
52 |  | 1 | FISCHER ELEKTRONIK | SK508-100SA | Heatsink; 100 x 25 x 100 mm |  |  | DNP
53 |  | 1 | ALUTRONIC | SI 6018 | Silicone isolation foil; 20x94x0,18 |  |  | DNP
54 |  | 4 | FISCHER ELEKTRONIK | IB 16 | Isolation bushing, M3 |  |  | DNP
55 |  | 4 |  | M3x20 screw with hexnut |  |  |  | DNP

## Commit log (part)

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2025-04-26 updated motionboard evoIII files
2026-03-23 Update README with contact info and Discord link
